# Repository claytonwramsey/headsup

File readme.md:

# Team HEADSUP Senior Design Repository

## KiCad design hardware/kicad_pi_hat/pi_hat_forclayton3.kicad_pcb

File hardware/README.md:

All Altium hardware files used in this project.

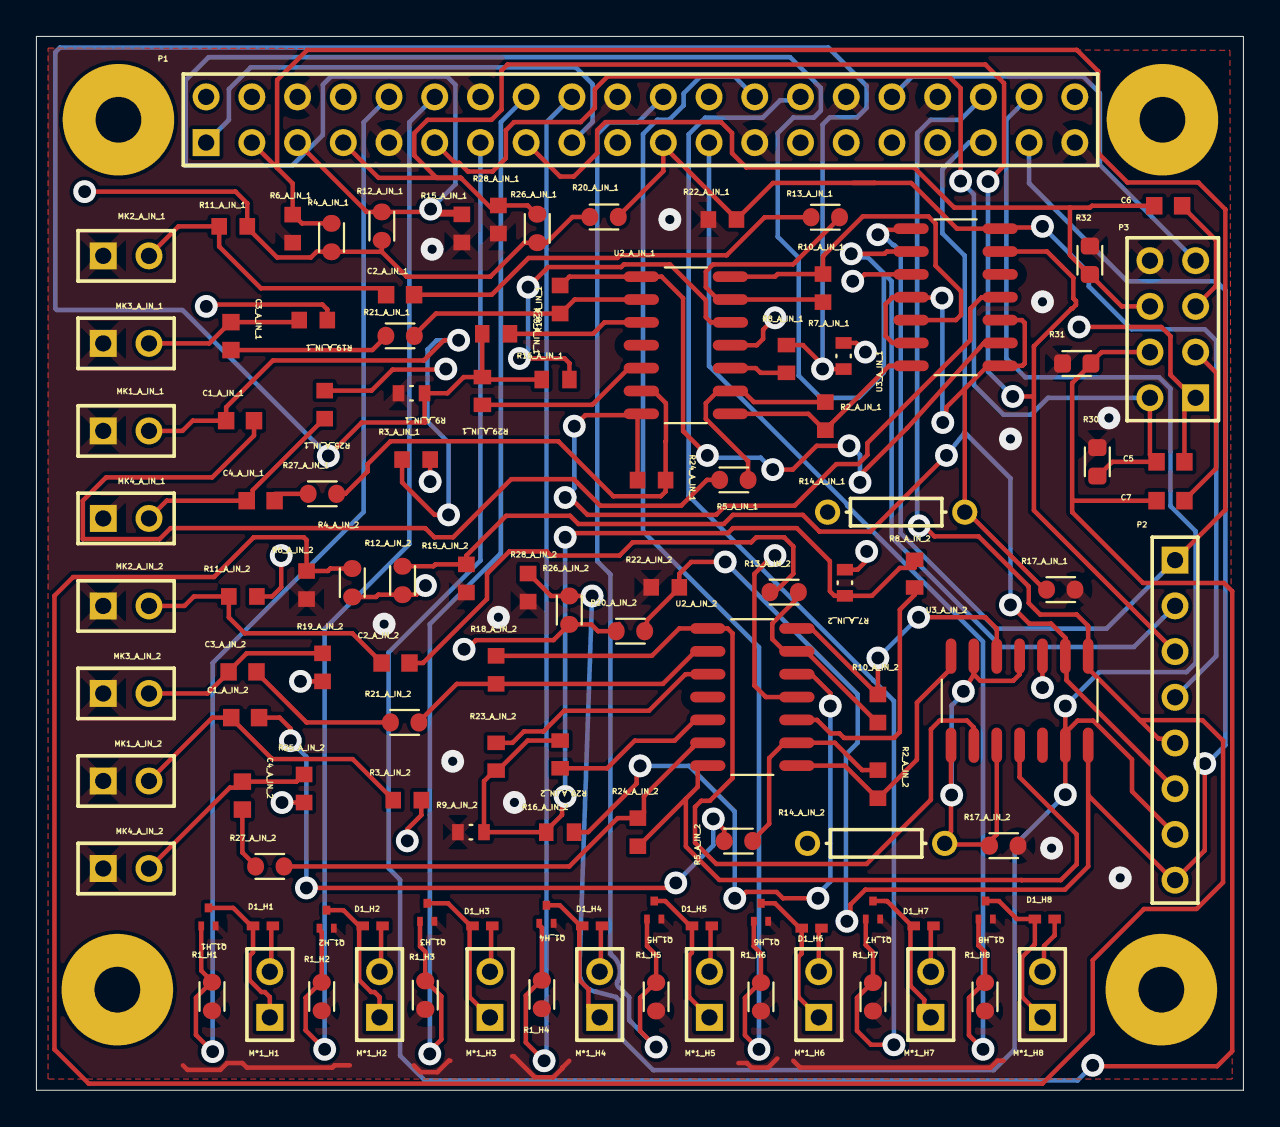
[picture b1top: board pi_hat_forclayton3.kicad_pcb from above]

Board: 4 copper layers, 67.1 x 58.5 mm, 117 parts (0 on the bottom side), 77 nets.

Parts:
C1_A_IN_1, C3_A_IN_1: 1uF; CAPC1608X87N_1
C1_A_IN_2: 1uF; CAPC1608X87N_2
C2_A_IN_1: 1uF; CAPC1608X87N_4
C2_A_IN_2, C3_A_IN_2: 1uF; CAPC1608X87N_6
C4_A_IN_1: 1uF; CAPC1608X87N_3
C4_A_IN_2: 1uF; CAPC1608X87N_5
C5, C6, C7: 06035C104KAT2A; CAPC1608X90N_1
D1_H1, D1_H2, D1_H3, D1_H4, D1_H5, D1_H6, D1_H7, D1_H8: 1PS79SB70; SOD523_1
M*1_H1, M*1_H2, M*1_H8: Haptic Motor; HDR1X2_1
M*1_H3, M*1_H4, M*1_H5: Haptic Motor; HDR1X2_2
M*1_H6, M*1_H7: Haptic Motor; HDR1X2_3
MK1_A_IN_1: Mic2; PIN2_1
MK1_A_IN_2, MK3_A_IN_1: Mic2; PIN2_2
MK2_A_IN_1, MK3_A_IN_2: Mic2; PIN2_4
MK2_A_IN_2: Mic2; PIN2_6
MK4_A_IN_1: Mic2; PIN2_3
MK4_A_IN_2: Mic2; PIN2_5
P1: Header 20X2; HDR2X20_1
P2: Header 8; HDR1X8_1
P3: Header 4X2; HDR2X4_1
Q1_H1: MOSFET-N; X1-DFN1212-3_1
Q1_H2, Q1_H3, Q1_H4, Q1_H6, Q1_H7: MOSFET-N; X1-DFN1212-3_2
Q1_H5: MOSFET-N; X1-DFN1212-3_3
Q1_H8: MOSFET-N; X1-DFN1212-3_4
R1_H1, R1_H2, R1_H7, R1_H8: 1k; RESC1608X50N_17
R1_H3: 1k; RESC1608X50N_18
R1_H4: 1k; RESC1608X50N_19
R1_H5: 1k; RESC1608X50N_20
R1_H6: 1k; RESC1608X50N_21
R2_A_IN_1, R24_A_IN_2: 100k; RESC1608X55N_3
R2_A_IN_2: 100k; RESC1608X55N_12
R3_A_IN_1, R11_A_IN_1: 2.2K; RESC1608X55N_1
R3_A_IN_2: 2.2K; RESC1608X55N_2
R4_A_IN_1, R12_A_IN_1, R26_A_IN_1: 1K; RESC1608X50N_5
R4_A_IN_2: 1K; RESC1608X50N_14
R5_A_IN_1: 1k; RESC1608X50N_3
R5_A_IN_2: 1k; RESC1608X50N_4
R6_A_IN_1, R19_A_IN_1, R22_A_IN_1, R25_A_IN_1: 2.2K; RESC1608X55N_3
R6_A_IN_2: 2.2K; RESC1608X55N_13
R7_A_IN_1, R9_A_IN_1: 470K; RES_ERJ3EKF4703V_1
R7_A_IN_2: 470K; RES_ERJ3EKF4703V_3
R8_A_IN_1: 1M; RESC1508X55N_1
R8_A_IN_2: 1M; RESC1508X55N_2
R9_A_IN_2: 470K; RES_ERJ3EKF4703V_2
R10_A_IN_1, R18_A_IN_1: 100k; RESC1608X55N_5
R10_A_IN_2: 100k; RESC1608X55N_9
R11_A_IN_2: 2.2K; RESC1608X55N_11
R12_A_IN_2, R26_A_IN_2: 1K; RESC1608X50N_10
R13_A_IN_1, R27_A_IN_1: 1k; RESC1608X50N_9
R13_A_IN_2: 1k; RESC1608X50N_12
R14_A_IN_1: Res1; AXIAL-0.3_1
R14_A_IN_2: Res1; AXIAL-0.3_2
R15_A_IN_1: 2.2K; RESC1608X55N_4
R15_A_IN_2: 2.2K; RESC1608X55N_10
R16_A_IN_1, R29_A_IN_1: 1M; RESC1508X55N_3
R16_A_IN_2: 1M; RESC1508X55N_7
R17_A_IN_1: 10k; RESC1608X50N_8
R17_A_IN_2: 10k; RESC1608X50N_16
R18_A_IN_2: 100k; RESC1608X55N_17
R19_A_IN_2: 2.2K; RESC1608X55N_8
R20_A_IN_1: 1K; RESC1608X50N_7
R20_A_IN_2: 1K; RESC1608X50N_11
R21_A_IN_1: 1k; RESC1608X50N_6
R21_A_IN_2: 1k; RESC1608X50N_13
R22_A_IN_2: 2.2K; RESC1608X55N_16
R23_A_IN_1: 1M; RESC1508X55N_4
R23_A_IN_2: 1M; RESC1508X55N_5
R24_A_IN_1: 100k; RESC1608X55N_7
R25_A_IN_2: 2.2K; RESC1608X55N_15
R27_A_IN_2: 1k; RESC1608X50N_15
R28_A_IN_1: 2.2K; RESC1608X55N_6
R28_A_IN_2: 2.2K; RESC1608X55N_14
R29_A_IN_2: 1M; RESC1508X55N_6
R30: CRGS0603J10K; RESC1608X50N_2
R31, R32: CRGS0603J10K; RESC1608X50N_1
U2_A_IN_1: OPA4196ID; SOIC127P600X175-14N_1
U2_A_IN_2: OPA4196ID; SOIC127P600X175-14N_4
U3_A_IN_1: TLC339CD; SOIC127P600X175-14N_2
U3_A_IN_2: TLC339CD; SOIC127P600X175-14N_3

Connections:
3.3V: P1.1, P1.17
5V: C5.1, D1_H1.1, D1_H2.1, D1_H3.1, D1_H4.1, D1_H5.1, D1_H6.1, D1_H7.1, D1_H8.1, M*1_H1.2, M*1_H2.2, M*1_H3.2, M*1_H4.2, M*1_H5.2, M*1_H6.2, M*1_H7.2, M*1_H8.2, P1.2, P1.4, P3.1, R3_A_IN_1.2, R3_A_IN_2.2, R4_A_IN_1.2, R4_A_IN_2.2, R7_A_IN_1.2, R7_A_IN_2.2, R11_A_IN_1.2, R11_A_IN_2.2, R12_A_IN_1.2, R12_A_IN_2.2, R14_A_IN_1.2, R14_A_IN_2.2, R19_A_IN_1.2, R19_A_IN_2.2, R20_A_IN_1.2, R20_A_IN_2.2, R25_A_IN_1.2, R25_A_IN_2.2, R26_A_IN_1.2, R26_A_IN_2.2, U2_A_IN_1.4, U2_A_IN_2.4, U3_A_IN_1.3, U3_A_IN_2.3
Button0: C5.2, P1.11, P3.2, R30.2
Button1: C7.2, P1.13, P3.4, R31.2
Button2: C6.2, P1.15, P3.6, R32.2
GND: MK1_A_IN_1.1, MK1_A_IN_2.1, MK2_A_IN_1.1, MK2_A_IN_2.1, MK3_A_IN_1.1, MK3_A_IN_2.1, MK4_A_IN_1.1, MK4_A_IN_2.1, P1.6, P1.9, P1.14, P1.20, P1.25, P1.30, P1.34, P1.39, P3.8, Q1_H1.3, Q1_H2.3, Q1_H3.3, Q1_H4.3, Q1_H5.3, Q1_H6.3, Q1_H7.3, Q1_H8.3, R1_H1.1, R1_H2.1, R1_H3.1, R1_H4.1, R1_H5.1, R1_H6.1, R1_H7.1, R1_H8.1, R6_A_IN_1.1, R6_A_IN_2.1, R9_A_IN_1.1, R9_A_IN_2.1, R15_A_IN_1.1, R15_A_IN_2.1, R17_A_IN_1.1, R17_A_IN_2.1, R22_A_IN_1.1, R22_A_IN_2.1, R28_A_IN_1.1, R28_A_IN_2.1, R30.1, R31.1, R32.1, U2_A_IN_1.11, U2_A_IN_2.11, U3_A_IN_1.12, U3_A_IN_2.12
GPIO_1: P1.28, Q1_H7.2, R1_H7.2
GPIO_7: P1.26, Q1_H6.2, R1_H6.2
GPIO_11: P1.23, Q1_H8.2, R1_H8.2
GPIO_12: P1.32, P3.7
GPIO_15: P1.10, Q1_H1.2, R1_H1.2
GPIO_18: P1.12, Q1_H2.2, R1_H2.2
GPIO_23: P1.16, Q1_H3.2, R1_H3.2
GPIO_24: P1.18, Q1_H4.2, R1_H4.2
GPIO_25: P1.22, Q1_H5.2, R1_H5.2
NetC1_A_in_1_1: C1_A_IN_1.1, R5_A_IN_1.1
NetC1_A_in_1_2: C1_A_IN_1.2, MK1_A_IN_1.2, R3_A_IN_1.1
NetC1_A_in_2_1: C1_A_IN_2.1, R5_A_IN_2.1
NetC1_A_in_2_2: C1_A_IN_2.2, MK1_A_IN_2.2, R3_A_IN_2.1
NetC2_A_in_1_1: C2_A_IN_1.1, R13_A_IN_1.1
NetC2_A_in_1_2: C2_A_IN_1.2, MK2_A_IN_1.2, R11_A_IN_1.1
NetC2_A_in_2_1: C2_A_IN_2.1, R13_A_IN_2.1
NetC2_A_in_2_2: C2_A_IN_2.2, MK2_A_IN_2.2, R11_A_IN_2.1
NetC3_A_in_1_1: C3_A_IN_1.1, R21_A_IN_1.1
NetC3_A_in_1_2: C3_A_IN_1.2, MK3_A_IN_1.2, R19_A_IN_1.1
NetC3_A_in_2_1: C3_A_IN_2.1, R21_A_IN_2.1
NetC3_A_in_2_2: C3_A_IN_2.2, MK3_A_IN_2.2, R19_A_IN_2.1
NetC4_A_in_1_1: C4_A_IN_1.1, R27_A_IN_1.1
NetC4_A_in_1_2: C4_A_IN_1.2, MK4_A_IN_1.2, R25_A_IN_1.1
NetC4_A_in_2_1: C4_A_IN_2.1, R27_A_IN_2.1
NetC4_A_in_2_2: C4_A_IN_2.2, MK4_A_IN_2.2, R25_A_IN_2.1
NetC6_1: C6.1, P3.5
NetC7_1: C7.1, P3.3
NetD1_H1_2: D1_H1.2, M*1_H1.1, Q1_H1.1
NetD1_H2_2: D1_H2.2, M*1_H2.1, Q1_H2.1
NetD1_H3_2: D1_H3.2, M*1_H3.1, Q1_H3.1
NetD1_H4_2: D1_H4.2, M*1_H4.1, Q1_H4.1
NetD1_H5_2: D1_H5.2, M*1_H5.1, Q1_H5.1
NetD1_H6_2: D1_H6.2, M*1_H6.1, Q1_H6.1
NetD1_H7_2: D1_H7.2, M*1_H7.1, Q1_H7.1
NetD1_H8_2: D1_H8.2, M*1_H8.1, Q1_H8.1
audio_ch_out_0: P1.3, P2.1, R4_A_IN_1.1, R6_A_IN_1.2, U3_A_IN_1.1
audio_ch_out_1: P1.5, P2.2, R12_A_IN_1.1, R15_A_IN_1.2, U3_A_IN_1.2
audio_ch_out_2: P1.7, P2.3, R26_A_IN_1.1, R28_A_IN_1.2, U3_A_IN_1.13
audio_ch_out_3: P1.21, P2.4, R20_A_IN_1.1, R22_A_IN_1.2, U3_A_IN_1.14
audio_ch_out_4: P1.36, P2.5, R4_A_IN_2.1, R6_A_IN_2.2, U3_A_IN_2.1
audio_ch_out_5: P1.35, P2.6, R12_A_IN_2.1, R15_A_IN_2.2, U3_A_IN_2.2
audio_ch_out_6: P1.38, P2.7, R26_A_IN_2.1, R28_A_IN_2.2, U3_A_IN_2.13
audio_ch_out_7: P1.37, P2.8, R20_A_IN_2.1, R22_A_IN_2.2, U3_A_IN_2.14
audio_ref_A_in_1: R14_A_IN_1.1, R17_A_IN_1.2, U3_A_IN_1.4, U3_A_IN_1.6, U3_A_IN_1.8, U3_A_IN_1.10
audio_ref_A_in_2: R14_A_IN_2.1, R17_A_IN_2.2, U3_A_IN_2.4, U3_A_IN_2.6, U3_A_IN_2.8, U3_A_IN_2.10
bias_A_in_1: R7_A_IN_1.1, R8_A_IN_1.1, R9_A_IN_1.2, R16_A_IN_1.1, R23_A_IN_1.1, R29_A_IN_1.1
bias_A_in_2: R7_A_IN_2.1, R8_A_IN_2.1, R9_A_IN_2.2, R16_A_IN_2.1, R23_A_IN_2.1, R29_A_IN_2.1
ch1_+1in_A_in_1: R8_A_IN_1.2, U2_A_IN_1.3
ch1_+1in_A_in_2: R8_A_IN_2.2, U2_A_IN_2.3
ch1_-1in_A_in_1: R2_A_IN_1.2, R5_A_IN_1.2, U2_A_IN_1.2
ch1_-1in_A_in_2: R2_A_IN_2.2, R5_A_IN_2.2, U2_A_IN_2.2
ch1_out1_A_in_1: R2_A_IN_1.1, U2_A_IN_1.1, U3_A_IN_1.7
ch1_out1_A_in_2: R2_A_IN_2.1, U2_A_IN_2.1, U3_A_IN_2.7
ch2_+2in_A_in_1: R16_A_IN_1.2, U2_A_IN_1.5
ch2_+2in_A_in_2: R16_A_IN_2.2, U2_A_IN_2.5
ch2_-2in_A_in_1: R10_A_IN_1.2, R13_A_IN_1.2, U2_A_IN_1.6
ch2_-2in_A_in_2: R10_A_IN_2.2, R13_A_IN_2.2, U2_A_IN_2.6
ch2_out2_A_in_1: R10_A_IN_1.1, U2_A_IN_1.7, U3_A_IN_1.5
ch2_out2_A_in_2: R10_A_IN_2.1, U2_A_IN_2.7, U3_A_IN_2.5
ch3_+3in_A_in_1: R23_A_IN_1.2, U2_A_IN_1.10
ch3_+3in_A_in_2: R23_A_IN_2.2, U2_A_IN_2.10
ch3_-3in_A_in_1: R18_A_IN_1.2, R21_A_IN_1.2, U2_A_IN_1.9
ch3_-3in_A_in_2: R18_A_IN_2.2, R21_A_IN_2.2, U2_A_IN_2.9
ch3_out3_A_in_1: R18_A_IN_1.1, U2_A_IN_1.8, U3_A_IN_1.9
ch3_out3_A_in_2: R18_A_IN_2.1, U2_A_IN_2.8, U3_A_IN_2.9
ch4_+4in_A_in_1: R29_A_IN_1.2, U2_A_IN_1.12
ch4_+4in_A_in_2: R29_A_IN_2.2, U2_A_IN_2.12
ch4_-4in_A_in_1: R24_A_IN_1.2, R27_A_IN_1.2, U2_A_IN_1.13
ch4_-4in_A_in_2: R24_A_IN_2.2, R27_A_IN_2.2, U2_A_IN_2.13
ch4_out4_A_in_1: R24_A_IN_1.1, U2_A_IN_1.14, U3_A_IN_1.11
ch4_out4_A_in_2: R24_A_IN_2.1, U2_A_IN_2.14, U3_A_IN_2.11

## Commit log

2023-01-23 copy over example code for camera
2023-01-23 implement columnar depth vision
2023-01-23 starting breaking things
2023-01-27 get object tracking running but it stops occasionally ???
2023-01-27 working vision pipeline
2023-01-27 Add proof of concept embedded software and project skeleton.
2023-02-02 Add skeleton Google Glass application.
2023-02-02 Added haptic control embedded software.
2023-02-02 rename to glass to make project name clear
2023-02-02 Add ADC code, IMU code, and update Glass configuration.
2023-02-02 add xml file for Glass hardware
2023-02-02 add queue creation for IMU device
2023-02-02 Fix error in referencing IMU object.
2023-02-02 amend import for device
2023-02-02 more import fixups
2023-02-02 blind copy
2023-02-03 restructure raspberry pi code to make it simpler
2023-02-03 notes on running main
2023-02-03 add pycache to gitignore
2023-02-03 move to using raw accelerometer and gyroscope
2023-02-03 remember to add device usage to main
2023-02-03 fix weird capital M in accelerometer
2023-02-03 rework IMU code
2023-02-03 hopefully resolve queue behavior?
2023-02-03 remember to add .packets
2023-02-03 amend madgwick interaction
2023-02-03 move Dt to initialization of filter
2023-02-03 try converting gyro/acc data to ndarrays
2023-02-03 fix misspelling of current_quaternion
2023-02-03 fix body of self.current_quaternion
2023-02-04 Convert (x,y,z) to (r,\theta) coordinates.
2023-02-04 Print out (r, \theta).
2023-02-04 Add missing import.
2023-02-04 Bug fix.
2023-02-04 Remove label set.
2023-02-04 Remove unnecessary print statements.
2023-02-04 Clear screen to observe tracklets.
2023-02-04 Fix previous commit.
2023-02-07 Code for flashing LED upon detecting pulse from analog channel.
2023-02-14 remove debug objects from git vcs
2023-02-14 add start on linear algebra in C; probably not going to be used
2023-02-14 create temp crate for audio system
2023-02-14 create demo for rising edges on audio system
2023-02-14 remove linalg timing C code as it was unnecessary
2023-02-14 my gradient descent solver doesn't work :(
2023-02-14 clean up step scaling
2023-02-15 found one bug with gradient descent but there are yet more
2023-02-15 add support for gpio2 on gpio test code
2023-02-15 update pinout for 8-channel prototype
2023-02-15 pin 14 not working, try moving to other pin
2023-02-15 hacky approach to adding insensitivity to terminals - see if they work
2023-02-15 Add MATLAB proof of concept for localization strategy.
2023-02-16 make edge detection more efficient with mutex competition
2023-02-16 gradient descent solver finally works!
2023-02-16 add tests for 3d sourcing
2023-02-17 create prototype code for localization via gradient descent
2023-02-17 copy over true numbers for mic locations
2023-02-17 resolve microphone logic error in atomic read
2023-02-17 resolve parallelism wonkiness in events storage
2023-02-18 hacky LLS localization
2023-02-18 add file output for event info
2023-02-18 amend csv format
2023-02-18 move to doubles for floats
2023-02-18 amend shit overwriting and hopefully this makes life better?
2023-02-18 add times printout
2023-02-18 write down predicted angle in results file
2023-02-18 cleaning up printouts and converting angles to degrees
2023-02-18 raise event duration to 1s to prevent impacts from echoing:
2023-02-18 add command line args for degrees and range
2023-02-18 actually write degrees and range to file
2023-02-18 Add results of 2/18 localization test.
2023-02-18 Add visualization for average accuracy of localization.
2023-02-19 Fix radar display code and add test file.
2023-02-19 Remove IDE files.
2023-02-20 Add IO test and integrate radar screen into main.py.
2023-02-20 Fix naming issue.
2023-02-20 Fix frame type issue in vision module.
2023-02-20 Fix bugs in interfacing display and vision modules.
2023-02-22 simplify direction computation logic
2023-02-22 documentation cleanup on localization algorithm
2023-02-23 slightly more efficient implementation on finding mininum time
2023-02-23 add start on kicad pcb; we'll see if it matters
2023-02-23 amend backups being pushed
2023-02-25 Test radar overlay on RGB image.
2023-02-25 Get RGB frame from spatial data queue.
2023-03-01 Revert "Get RGB frame from spatial data queue."
    This reverts commit 1543cb68b3d1231560067506a992fdf1e69c3495.
2023-03-01 remove unused code and designs
2023-03-01 clean up audio code
2023-03-01 remove degrees/range printout
2023-03-05 Test IO module.
2023-03-05 Fix naming collision.
2023-03-05 Verified user io module works..
2023-03-06 create demo haptic output code?
2023-03-11 Updated IMU code for Oak-D Wide camera.
2023-03-11 Integrate new orientation module with main.
2023-03-13 Mirror radar display.
2023-03-13 create haptics test binary
2023-03-13 Testing PWM on pin 17.
2023-03-13 Haptic output test.
2023-03-13 Only one output pin.
2023-03-13 Fix haptics test code.
2023-03-13 Fix buzzer period.
2023-03-21 Add client-requested UI elements.
2023-03-21 Fix IMU rotation vector acquisition bug
2023-03-21 Fix IMU packet bug
2023-03-21 Fix radius type
2023-03-21 Fix FOV line drawing
2023-03-21 Add waitKey for debugging
2023-03-21 Fix the distance rings on the radar screen
2023-03-21 UI updates
2023-03-23 Updated UI to constrain UI to box.
2023-03-23 Move radar screen above rear view.
2023-03-23 Fix issue with display window disappearing.
2023-03-23 Print.
2023-03-23 Test.
2023-03-23 Test prints.
2023-03-23 Separate windows.
2023-03-23 Pivot to separable screen.
2023-03-23 Remove location information.
2023-03-24 create start on 3D solidworks models
2023-03-24 remove tilde files
2023-03-24 try adding tildefiles to gitignore
2023-03-25 UI updates and Altium files.
2023-03-25 create kicad importation of pi hat
2023-03-25 create v3 gerbers
2023-03-25 not sure what I did but kicad made me edit the pcb
2023-03-27 Add 1200x1200 RESNET blob.
2023-03-29 Update text in UI
2023-03-29 Fix font size.
2023-03-29 Update to new tracking model.
2023-03-29 Fix typo
2023-03-29 Push 1200x1200 input
2023-04-08 create microphone and battery casement
